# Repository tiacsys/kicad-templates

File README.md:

# KiCad Templates

This repository contains the official KiCad project and worksheet templates.

Contribution guidelines can be found at http://kicad.org/libraries/contribute
The library convention can be found at http://kicad.org/libraries/klc/

Other KiCad library repositories are located:

* Symbols: https://gitlab.com/kicad/libraries/kicad-symbols
* Footprints: https://gitlab.com/kicad/libraries/kicad-footprints
* 3D Models: https://gitlab.com/kicad/libraries/kicad-packages3d

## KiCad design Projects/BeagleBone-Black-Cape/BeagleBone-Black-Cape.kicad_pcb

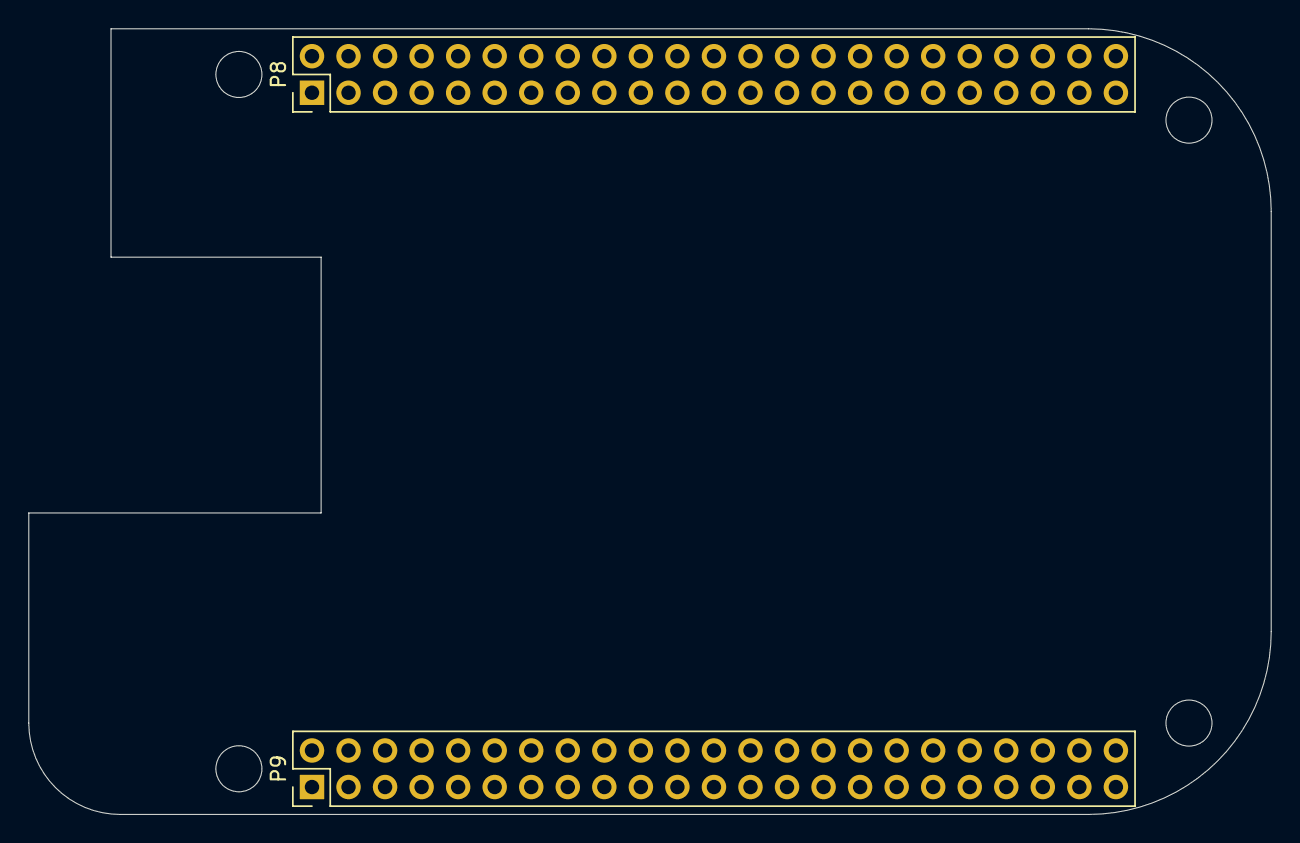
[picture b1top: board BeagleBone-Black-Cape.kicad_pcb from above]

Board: 2 copper layers, 86.4 x 54.6 mm, 6 parts (0 on the bottom side), 4 nets, no tracks yet.

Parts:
MH1, MH2, MH3, MH4: MountingHole_3.2mm_M3_DIN965
P8, P9: BeagleBone_Black_Header; PinHeader_2x23_P2.54mm_Vertical

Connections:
+3V3: P9.3, P9.4
+5V: P9.5, P9.6
GNDD: P8.1, P8.2, P8.45, P9.1, P9.2, P9.43, P9.44, P9.45, P9.46
VBUS: P9.7, P9.8

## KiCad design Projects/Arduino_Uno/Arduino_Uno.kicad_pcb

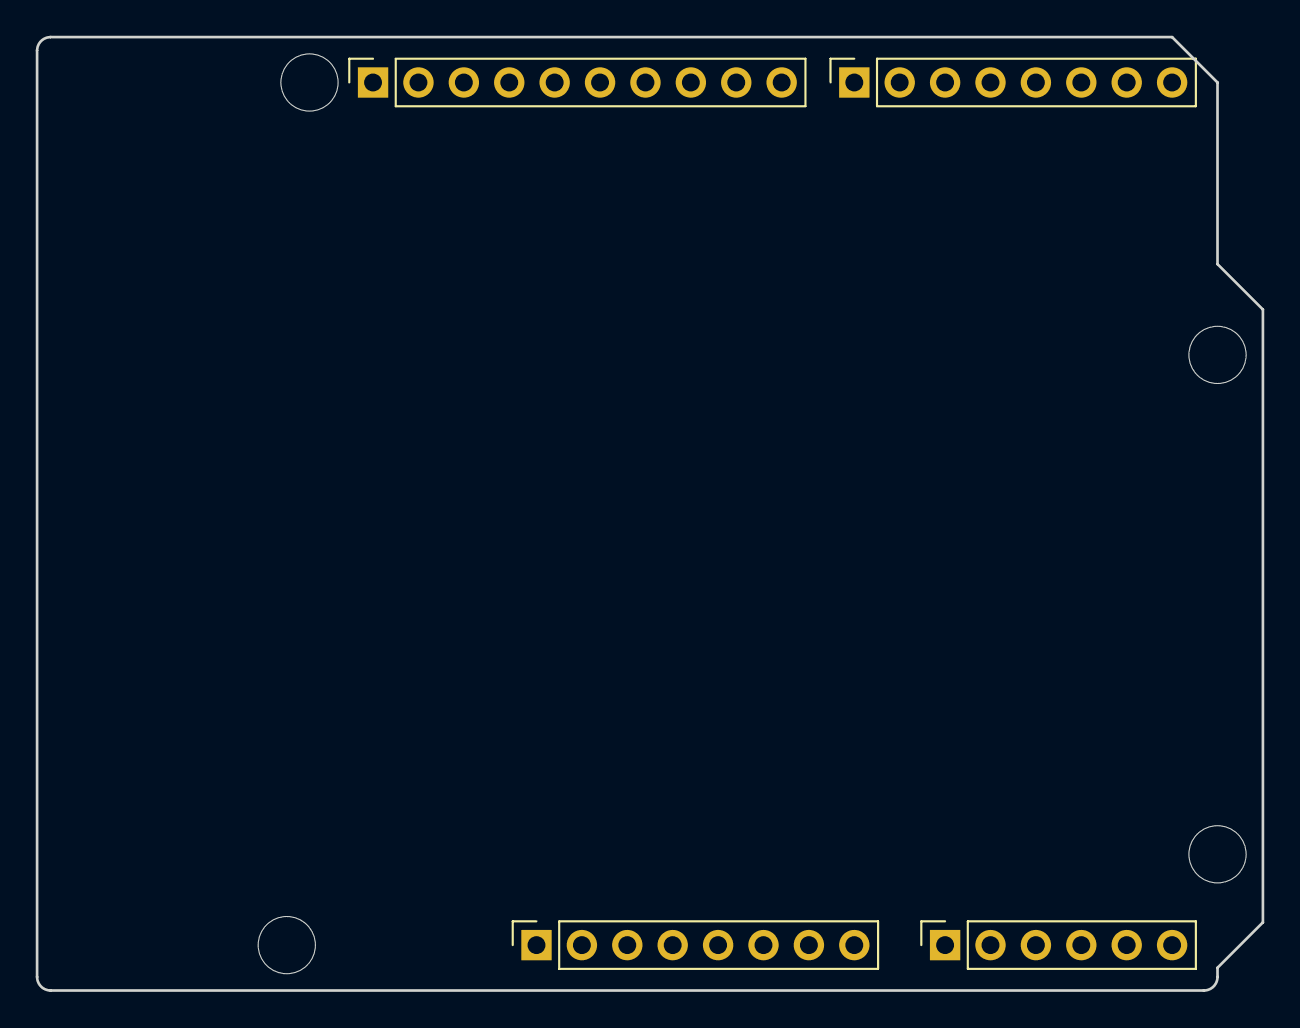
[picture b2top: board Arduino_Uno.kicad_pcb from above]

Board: 2 copper layers, 68.6 x 53.3 mm, 8 parts (0 on the bottom side), 3 nets, no tracks yet.

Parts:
J1: Power; PinSocket_1x08_P2.54mm_Vertical
J2: Digital/PWM; PinSocket_1x10_P2.54mm_Vertical
J3: Analog; PinSocket_1x06_P2.54mm_Vertical
J4: Digital/PWM; PinSocket_1x08_P2.54mm_Vertical
MH1, MH2, MH3, MH4: MountingHole_3.2mm

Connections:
/SCL/A5: J2.1, J3.6
/SDA/A4: J2.2, J3.5
GND: J1.6, J1.7, J2.4

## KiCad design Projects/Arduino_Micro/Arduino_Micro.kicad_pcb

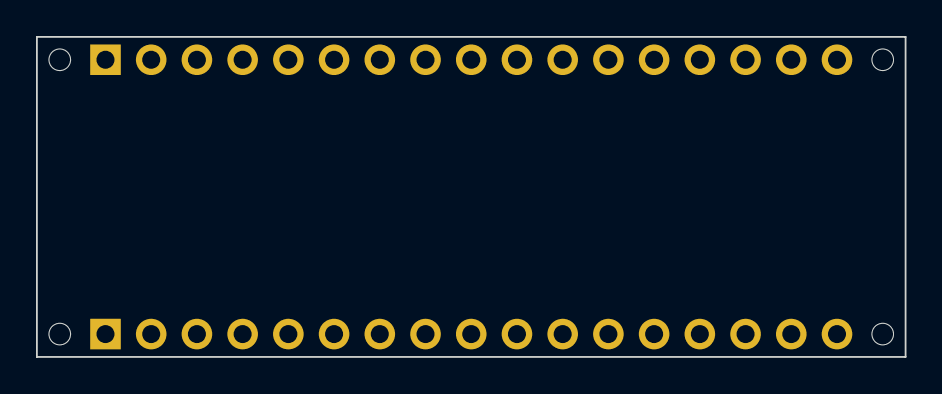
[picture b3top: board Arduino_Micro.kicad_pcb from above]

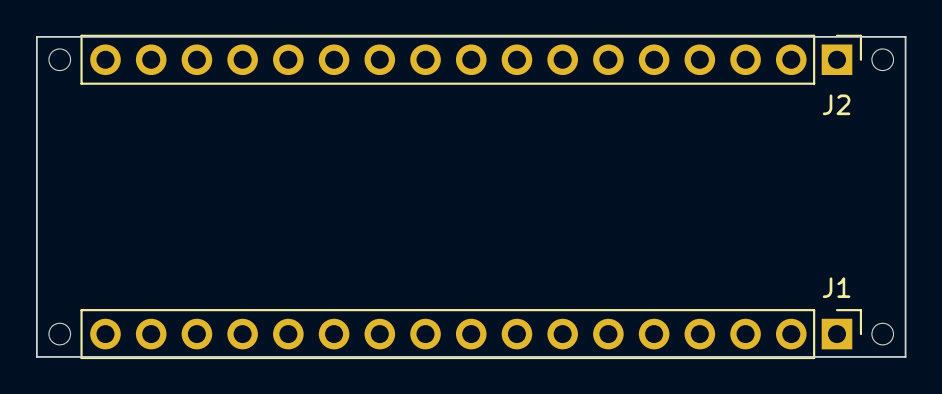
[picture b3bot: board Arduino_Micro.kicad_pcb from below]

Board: 2 copper layers, 48.3 x 17.8 mm, 6 parts (2 on the bottom side), 2 nets, no tracks yet.

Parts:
J1: Analog; PinHeader_1x17_P2.54mm_Vertical
J2: Digital; PinHeader_1x17_P2.54mm_Vertical
MH1, MH2, MH3, MH4: MountingHole_1.2mm

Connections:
/~RESET: J1.13, J2.13
GND: J1.14, J2.12

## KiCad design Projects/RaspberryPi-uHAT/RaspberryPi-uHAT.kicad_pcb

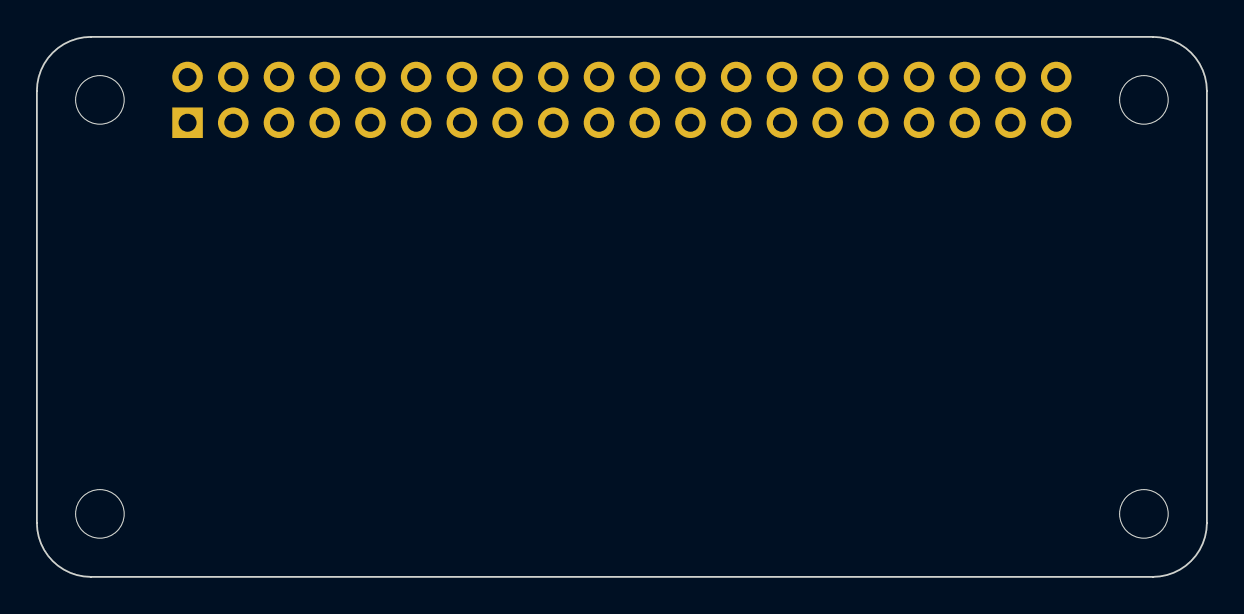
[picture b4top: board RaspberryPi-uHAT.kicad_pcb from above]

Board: 2 copper layers, 65.0 x 30.0 mm, 5 parts (1 on the bottom side), 3 nets, no tracks yet.

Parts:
J1: GPIO; PinSocket_2x20_P2.54mm_Vertical
MH1, MH2, MH3, MH4: MountingHole_2.7mm_M2.5

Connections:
+3V3: J1.1, J1.17
+5V: J1.2, J1.4
GND: J1.6, J1.9, J1.14, J1.20, J1.25, J1.30, J1.34, J1.39

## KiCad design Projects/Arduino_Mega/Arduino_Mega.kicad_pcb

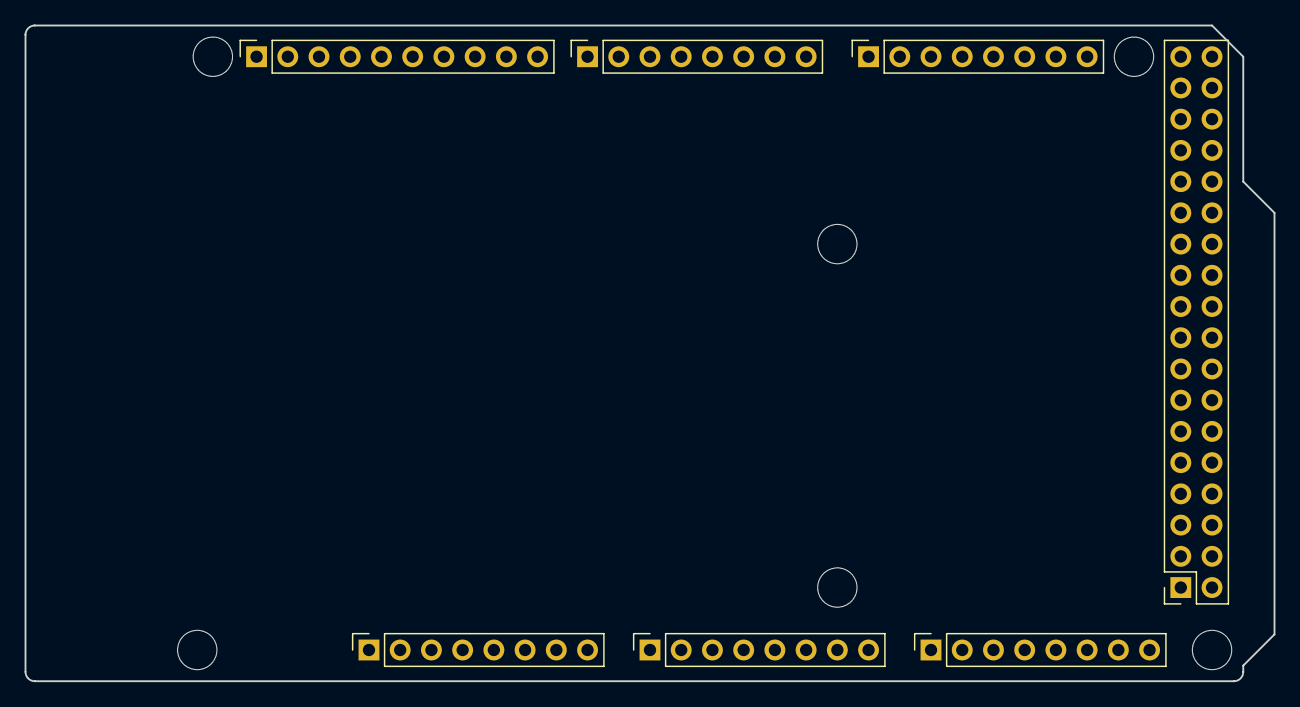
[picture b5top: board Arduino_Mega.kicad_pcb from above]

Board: 2 copper layers, 101.6 x 53.3 mm, 13 parts (0 on the bottom side), 4 nets, no tracks yet.

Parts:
J1: Power; PinSocket_1x08_P2.54mm_Vertical
J2: PWM; PinSocket_1x10_P2.54mm_Vertical
J3, J5: Analog; PinSocket_1x08_P2.54mm_Vertical
J4: PWM; PinSocket_1x08_P2.54mm_Vertical
J6: Communication; PinSocket_1x08_P2.54mm_Vertical
J7: Digital; PinSocket_2x18_P2.54mm_Vertical
MH1, MH2, MH3, MH4, MH5, MH6: MountingHole_3.2mm

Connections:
+5V: J1.5, J7.35, J7.36
/SCL/21: J2.1, J6.8
/SDA/20: J2.2, J6.7
GND: J1.6, J1.7, J2.4, J7.1, J7.2

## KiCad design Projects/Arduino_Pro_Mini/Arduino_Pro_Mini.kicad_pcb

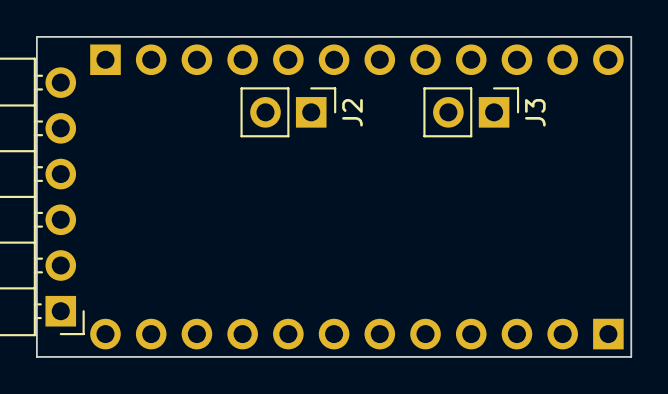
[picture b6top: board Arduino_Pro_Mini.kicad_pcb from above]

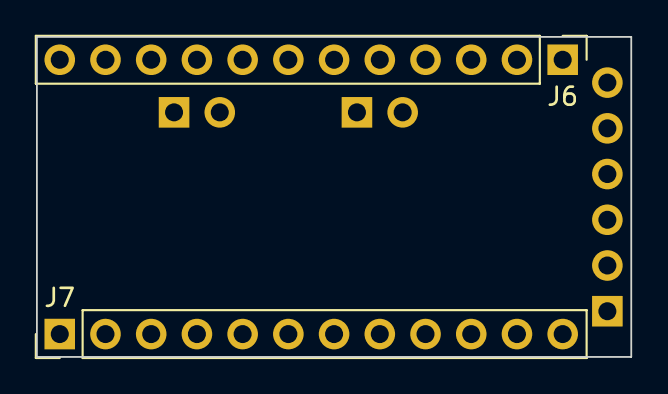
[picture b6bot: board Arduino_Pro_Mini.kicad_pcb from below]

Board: 2 copper layers, 33.0 x 17.8 mm, 5 parts (2 on the bottom side), 5 nets, no tracks yet.

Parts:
J1: FTDI; PinHeader_1x06_P2.54mm_Horizontal
J2: I2C; PinHeader_1x02_P2.54mm_Vertical
J3: Analog; PinHeader_1x02_P2.54mm_Vertical
J6: Analog; PinHeader_1x12_P2.54mm_Vertical
J7: Digital; PinHeader_1x12_P2.54mm_Vertical

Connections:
/RX: J1.4, J7.11
/TX: J1.5, J7.12
/~RESET: J6.3, J7.10
GND: J1.1, J1.2, J6.2, J7.9
VCC: J1.3, J6.4

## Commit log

2020-10-02 Remove deprecation
2020-12-31 Update projects to use new KICAD6 env var
2021-02-16 Update existing templates to version 6
2021-10-20 Change website URL
2021-10-20 Change website URL to kicad.org
2022-01-02 Bump cmake minimum version
2022-05-18 Update templates for KiCad 6
2023-01-06 Update projects for KiCad version 7
2023-01-22 Update to V7 vars
2023-02-11 Add Aisler example template
2023-09-23 Move cmake version requirement to above project line to stop cmake complaining on releases
2023-11-08 Add some templates useful for doing MR dimensioned drawings
    See merge request kicad/libraries/kicad-templates!51
2024-01-20 Remove project local settings
2024-01-20 Update templates to V8 format
2024-02-20 Correct BeagleBone Black pinout
2024-04-04 Update README.md with links to guidelines and other repos.
2024-05-01 Added STM32H7xx DevEBox template
2024-05-01 Add Template for API Series 500 PCB.
    Standard Audio in Pro (Studio) environment.
2024-05-13 Add STM32 Nucleo-64 boards template
2024-05-24 Templates: added Edgeberry Hardware Cartridge template
2024-12-17 Update - Edgeberry Template improve documentation, make mounting hole manufacturable, include template for faceplate.
2025-02-18 Manually convert all template project to v9
    Unfortunately there is no kicad-cli command which allows to automate the
    update of our template.
    So every single template has to be opened as a project, then schematic
    and board need to be individually saved. Same for included symbols and
    footprints.
    While at it, I also updated symbols and footprints in the respective
